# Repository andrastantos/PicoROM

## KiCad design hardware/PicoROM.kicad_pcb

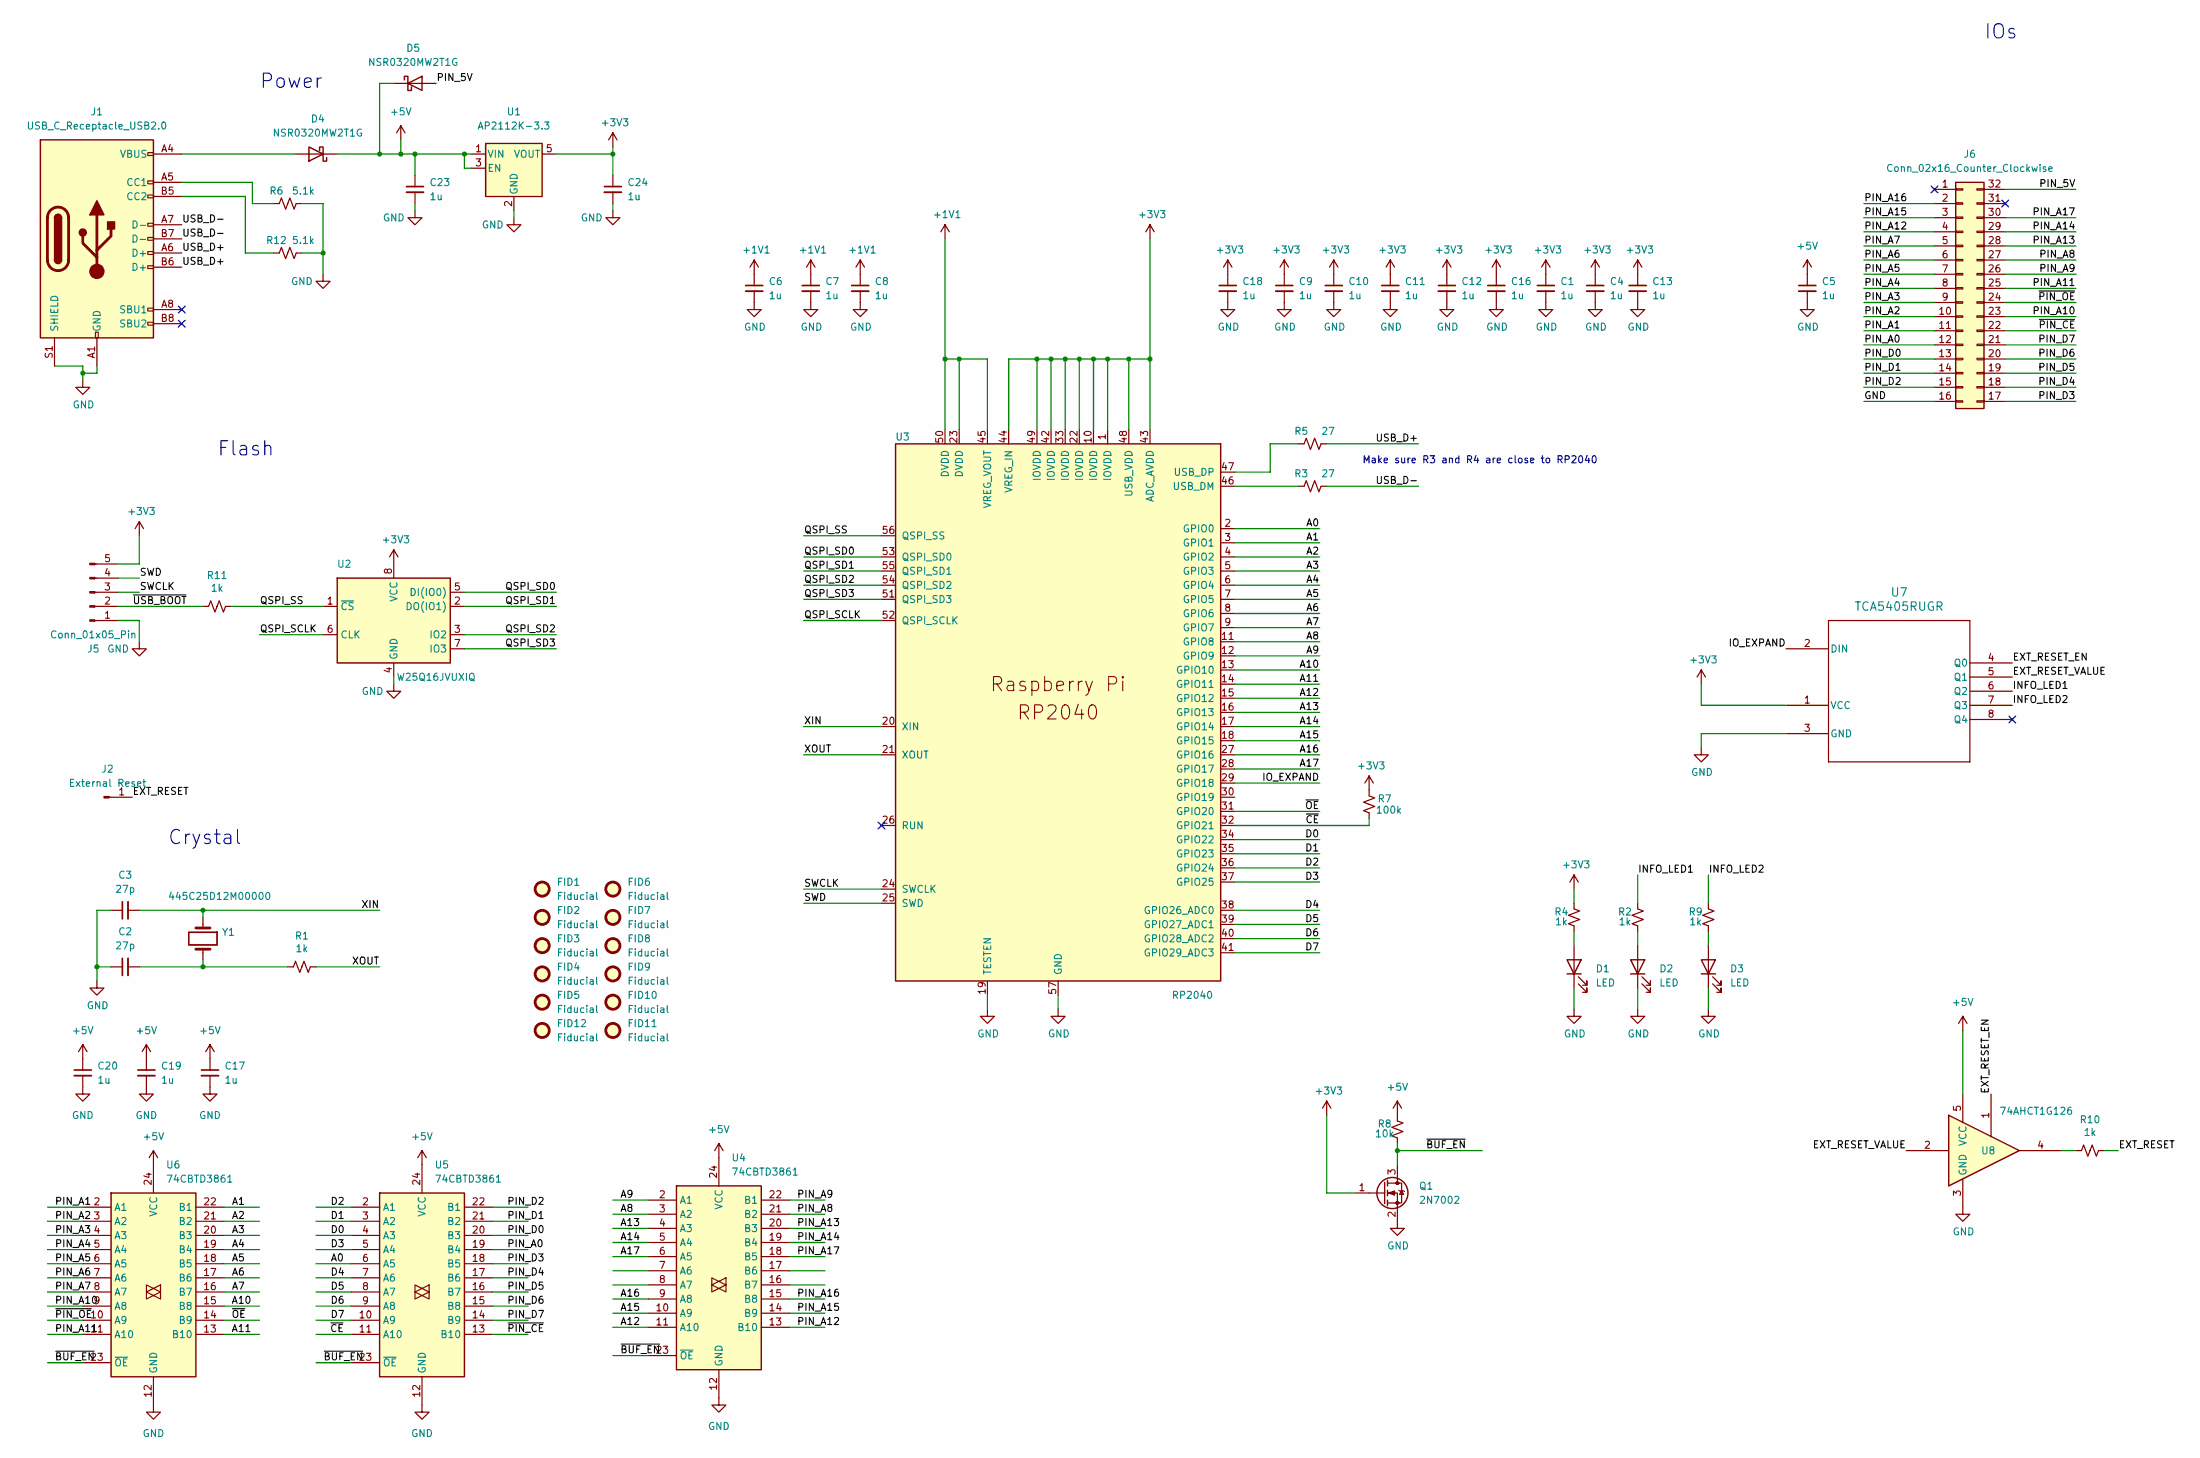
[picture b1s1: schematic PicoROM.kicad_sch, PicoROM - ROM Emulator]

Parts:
C1, C4, C5, C6, C7, C8, C9, C10, C11, C12, C13, C16, C17, C18, C19, C20, C23, C24: 1u; C_0402_1005Metric_Pad0.74x0.62mm_HandSolder
C2, C3: 27p; C_0402_1005Metric_Pad0.74x0.62mm_HandSolder
D1: LED; LED_0603_1608Metric; MPN C510027
D2: LED; LED_0603_1608Metric; MPN C2922668
D3: LED; LED_0603_1608Metric; MPN C2925173
D4, D5: NSR0320MW2T1G; D_SOD-323; MPN C48192
FID1, FID2, FID3, FID4, FID5, FID6, FID7, FID8, FID9, FID10, FID11, FID12: Fiducial; Fiducial_0.5mm_Mask1mm
J1: USB_C_Receptacle_USB2.0; USB_C_Receptacle_G-Switch_GT-USB-7051x; MPN C2843970
J2: External Reset; TestPoint_Pad_D3.0mm
J5: Conn_01x05_Pin; PinHeader_1x05_P1.00mm_Vertical
J6: Conn_02x16_Counter_Clockwise; DIP-32_pin_header
Q1: 2N7002; SOT-23
R1, R2, R4, R9, R10, R11: 1k; R_0402_1005Metric_Pad0.72x0.64mm_HandSolder
R3, R5: 27; R_0402_1005Metric_Pad0.72x0.64mm_HandSolder
R6, R12: 5.1k; R_0402_1005Metric_Pad0.72x0.64mm_HandSolder
R7: 100k; R_0402_1005Metric_Pad0.72x0.64mm_HandSolder
R8: 10k; R_0402_1005Metric_Pad0.72x0.64mm_HandSolder
U1: AP2112K-3.3; SOT-23-5; MPN C51118
U2: W25Q16JVUXIQ; Winbond_USON-8-1EP_3x2mm_P0.5mm_EP0.2x1.6mm; MPN C2843335
U3: RP2040; RP2040-QFN-56; MPN C2040
U4, U5, U6: 74CBTD3861; TSSOP-24_4.4x5mm_P0.4mm
U7: TCA5405RUGR; X2QFN-8_L1.5-W1.5-P0.50-BL; MPN C2674123
U8: 74AHCT1G126; SOT-23-5; MPN C163712
Y1: 445C25D12M00000; Crystal_SMD_5032-2Pin_5.0x3.2mm; MPN C148313

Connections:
+1V1: C6.1, C7.1, C8.1, U3.23 (DVDD), U3.45 (VREG_VOUT), U3.50 (DVDD)
+3V3: C1.1, C4.1, C9.1, C10.1, C11.1, C12.1, C13.1, C16.1, C18.1, C24.1, J5.5, Q1.1 (G), R4.2, R7.2, U1.5 (VOUT), U2.8 (VCC), U3.1 (IOVDD), U3.10 (IOVDD), U3.22 (IOVDD), U3.33 (IOVDD), U3.42 (IOVDD), U3.43 (ADC_AVDD), U3.44 (VREG_IN), U3.48 (USB_VDD), U3.49 (IOVDD), U7.1 (VCC)
+5V: C5.1, C17.1, C19.1, C20.1, C23.1, D4.1 (K), D5.1 (K), R8.2, U1.1 (VIN), U1.3 (EN), U4.24 (VCC), U5.24 (VCC), U6.24 (VCC), U8.5 (VCC)
/A0: U3.2 (GPIO0), U5.6 (A5)
/A1: U3.3 (GPIO1), U6.22 (B1)
/A2: U3.4 (GPIO2), U6.21 (B2)
/A3: U3.5 (GPIO3), U6.20 (B3)
/A4: U3.6 (GPIO4), U6.19 (B4)
/A5: U3.7 (GPIO5), U6.18 (B5)
/A6: U3.8 (GPIO6), U6.17 (B6)
/A7: U3.9 (GPIO7), U6.16 (B7)
/A8: U3.11 (GPIO8), U4.3 (A2)
/A9: U3.12 (GPIO9), U4.2 (A1)
/A10: U3.13 (GPIO10), U6.15 (B8)
/A11: U3.14 (GPIO11), U6.13 (B10)
/A12: U3.15 (GPIO12), U4.11 (A10)
/A13: U3.16 (GPIO13), U4.4 (A3)
/A14: U3.17 (GPIO14), U4.5 (A4)
/A15: U3.18 (GPIO15), U4.10 (A9)
/A16: U3.27 (GPIO16), U4.9 (A8)
/A17: U3.28 (GPIO17), U4.6 (A5)
/D0: U3.34 (GPIO22), U5.4 (A3)
/D1: U3.35 (GPIO23), U5.3 (A2)
/D2: U3.36 (GPIO24), U5.2 (A1)
/D3: U3.37 (GPIO25), U5.5 (A4)
/D4: U3.38 (GPIO26_ADC0), U5.7 (A6)
/D5: U3.39 (GPIO27_ADC1), U5.8 (A7)
/D6: U3.40 (GPIO28_ADC2), U5.9 (A8)
/D7: U3.41 (GPIO29_ADC3), U5.10 (A9)
/EXT_RESET: J2.1, R10.2
/EXT_RESET_EN: U7.4 (Q0), U8.1
/EXT_RESET_VALUE: U7.5 (Q1), U8.2
/INFO_LED1: R2.2, U7.6 (Q2)
/INFO_LED2: R9.2, U7.7 (Q3)
/IO_EXPAND: U3.29 (GPIO18), U7.2 (DIN)
/PIN_5V: D5.2 (A), J6.32
/PIN_A0: J6.12, U5.19 (B4)
/PIN_A1: J6.11, U6.2 (A1)
/PIN_A2: J6.10, U6.3 (A2)
/PIN_A3: J6.9, U6.4 (A3)
/PIN_A4: J6.8, U6.5 (A4)
/PIN_A5: J6.7, U6.6 (A5)
/PIN_A6: J6.6, U6.7 (A6)
/PIN_A7: J6.5, U6.8 (A7)
/PIN_A8: J6.27, U4.21 (B2)
/PIN_A9: J6.26, U4.22 (B1)
/PIN_A10: J6.23, U6.9 (A8)
/PIN_A11: J6.25, U6.11 (A10)
/PIN_A12: J6.4, U4.13 (B10)
/PIN_A13: J6.28, U4.20 (B3)
/PIN_A14: J6.29, U4.19 (B4)
/PIN_A15: J6.3, U4.14 (B9)
/PIN_A16: J6.2, U4.15 (B8)
/PIN_A17: J6.30, U4.18 (B5)
/PIN_D0: J6.13, U5.20 (B3)
/PIN_D1: J6.14, U5.21 (B2)
/PIN_D2: J6.15, U5.22 (B1)
/PIN_D3: J6.17, U5.18 (B5)
/PIN_D4: J6.18, U5.17 (B6)
/PIN_D5: J6.19, U5.16 (B7)
/PIN_D6: J6.20, U5.15 (B8)
/PIN_D7: J6.21, U5.14 (B9)
/QSPI_SCLK: U2.6 (CLK), U3.52 (QSPI_SCLK)
/QSPI_SD0: U2.5 (DI(IO0)), U3.53 (QSPI_SD0)
/QSPI_SD1: U2.2 (DO(IO1)), U3.55 (QSPI_SD1)
/QSPI_SD2: U2.3 (IO2), U3.54 (QSPI_SD2)
/QSPI_SD3: U2.7 (IO3), U3.51 (QSPI_SD3)
/QSPI_SS: R11.2, U2.1 (~CS), U3.56 (QSPI_SS)
/SWCLK: J5.3, U3.24 (SWCLK)
/SWD: J5.4, U3.25 (SWD)
/USB_D+: J1.A6 (D+), J1.B6 (D+), R5.2
/USB_D-: J1.A7 (D-), J1.B7 (D-), R3.2
/XIN: C3.2, U3.20 (XIN), Y1.1
/XOUT: R1.2, U3.21 (XOUT)
/~BUF_EN: Q1.3 (D), R8.1, U4.23 (~OE), U5.23 (~OE), U6.23 (~OE)
/~CE: R7.1, U3.32 (GPIO21), U5.11 (A10)
/~OE: U3.31 (GPIO20), U6.14 (B9)
/~PIN_CE: J6.22, U5.13 (B10)
/~PIN_OE: J6.24, U6.10 (A9)
/~USB_BOOT: J5.2, R11.1
GND: C1.2, C2.1, C3.1, C4.2, C5.2, C6.2, C7.2, C8.2, C9.2, C10.2, C11.2, C12.2, C13.2, C16.2, C17.2, C18.2, C19.2, C20.2, C23.2, C24.2, D1.1 (K), D2.1 (K), D3.1 (K), J1.A1 (GND), J1.A12 (GND), J1.B1 (GND), J1.B12 (GND), J1.S1 (SHIELD), J5.1, J6.16, Q1.2 (S), R6.2, R12.2, U1.2 (GND), U2.4 (GND), U3.19 (TESTEN), U3.57 (GND), U4.12 (GND), U5.12 (GND), U6.12 (GND), U7.3 (GND), U8.3 (GND)
unnamed: C2.2, R1.1, Y1.2
unnamed: D1.2 (A), R4.1
unnamed: D2.2 (A), R2.1
unnamed: D3.2 (A), R9.1
unnamed: D4.2 (A), J1.A4 (VBUS), J1.A9 (VBUS), J1.B4 (VBUS), J1.B9 (VBUS)
unnamed: J1.A5 (CC1), R6.1
unnamed: J1.B5 (CC2), R12.1
unnamed: R10.1, U8.4
unnamed: R3.1, U3.46 (USB_DM)
unnamed: R5.1, U3.47 (USB_DP)

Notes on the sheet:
Flash
Power
Make sure R3 and R4 are close to RP2040
Crystal
IOs

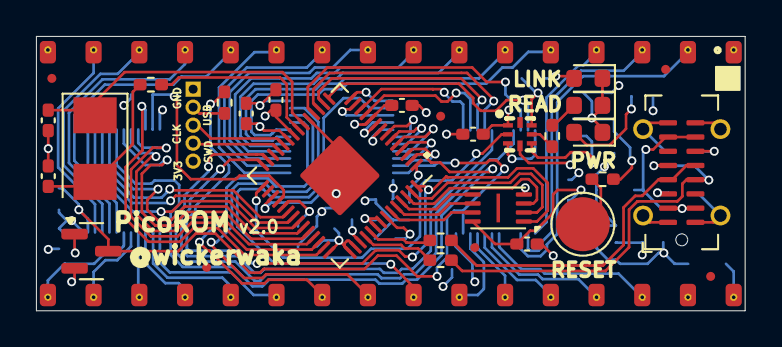
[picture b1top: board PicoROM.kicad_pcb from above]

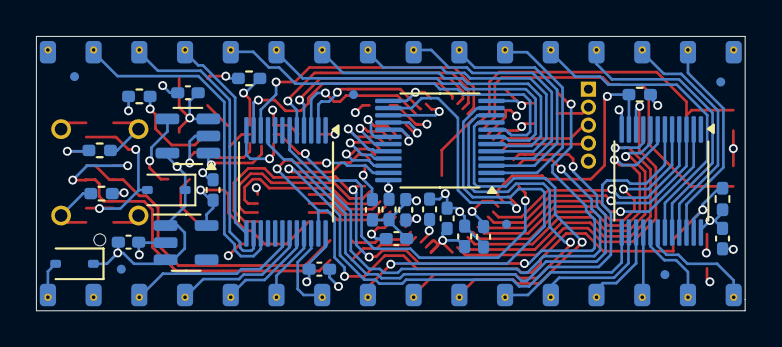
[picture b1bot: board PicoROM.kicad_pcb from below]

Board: 4 copper layers, 39.4 x 15.2 mm, 63 parts (32 on the bottom side), 91 nets.

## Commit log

2024-12-27 Redesigned ROM emulator.
    Changes from the original:
    - 4 layer PCB (not 6)
    - different level shifters
    - 0402 resistors and caps
    - reworked ~OE for level shifters
    - added fiducials
